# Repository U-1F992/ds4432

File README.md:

# DS4432

https://www.analog.com/products/ds4432.html

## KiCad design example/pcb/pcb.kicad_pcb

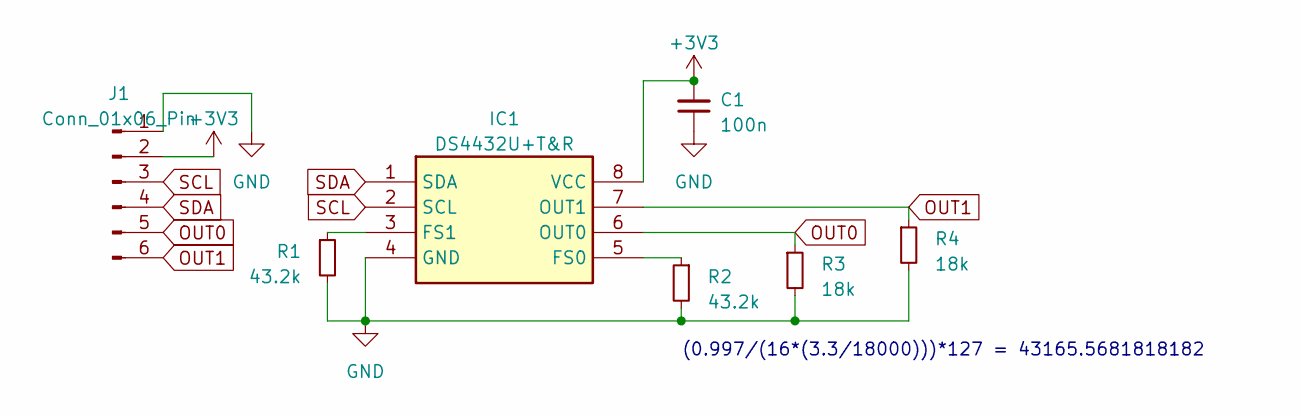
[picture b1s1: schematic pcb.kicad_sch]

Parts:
C1: 100n; C_0603_1608Metric
IC1: DS4432U+T&R; SOP65P490X110-8N; Mouser Part Number 700-DS4432UT&R
J1: Conn_01x06_Pin; PinHeader_1x06_P2.54mm_Vertical
R1, R2: 43.2k; R_0603_1608Metric
R3, R4: 18k; R_0603_1608Metric

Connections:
+3V3: C1.2, IC1.8 (VCC), J1.2
GND: C1.1, IC1.4 (GND), J1.1, R1.2, R2.2, R3.2, R4.2
unnamed: IC1.5 (FS0), R2.1
unnamed: IC1.3 (FS1), R1.1
OUT0: IC1.6 (OUT0), J1.5, R3.1
OUT1: IC1.7 (OUT1), J1.6, R4.1
SCL: IC1.2 (SCL), J1.3
SDA: IC1.1 (SDA), J1.4

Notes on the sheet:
(0.997/(16*(3.3/18000)))*127 = 43165.5681818182

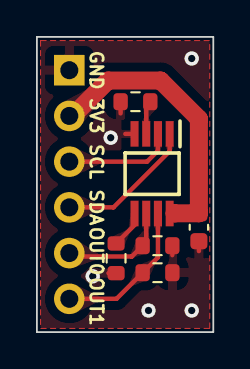
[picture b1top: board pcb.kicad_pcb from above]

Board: 2 copper layers, 9.8 x 16.4 mm, 7 parts (1 on the bottom side), 8 nets.

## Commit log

2024-02-18 Add Arduino example
2024-02-19 Fix I2C transmission
2024-02-19 Add pcb
2024-02-19 Add lib
2024-02-19 Update pcb
2024-03-03 Add test circuit
2024-03-05 Rename arduino.h to Arduino.h
2024-03-05 Renme arduino to Arduino
